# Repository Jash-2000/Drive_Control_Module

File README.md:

# Drive_Control_Module
Designed and Developed the Drive Control module for an Formula Electric car using ARM cortex processor.

---

## CAN - Controller Area Network

CAN provides four different types of message frames:

1. Data Frame – Sends data
Data transfer from one sending node to one or numerous receiving nodes.

2. Remote Frame – Requests data

Any node may request data from one source node. A remote frame is consequently followed by a data frame containing the requested data.

3. Error Frame – Reports error condition
Any bus participant, sender or receiver, may signal an error condition at any time during a data or remote frame transmission.

4. Overload Frame – Reports node overload

A node can request a delay between two data or remote frames, meaning that the overload frame can only occur between data or remote frame transmissions.

---

## Topics 

Vehicle Dynamics
```
  Wheel alignment
  Roll, yaw, pitch
  ABS
  Types of suspension, braking, brake fluid
  UV joints, rack & pinion
  Oversteer, understeer, counter-steer
  Load transfer
  Bearings
```

Aerodynamics
```
Lift & Drag (types and causes)
Centre of pressure
Coanda effect
Ground effect
Basic Airfoil terminology
Chassis and Ergonomics
Chassis Flex
Chassis stiffness
Different types of chassis
Composites used for making chassis
```

Powertrain
```
Thermodynamic cycles in engine.
All parts of engine, intake, exhaust.
Restrictor
Compression Ratio
Knocking
Torque steer elimination
CV and other types of joints
Differential: working and need
Volumetric efficiency
Chain tensioning methods
Engine tuning parameters
```

Electronics and Safety Circuits
```
Sensors
DAQ (Data Acquisition System)
T-MAP sensors
Relays
Solenoids
Shutdown/kill switches
Rectifier
Diodes
Motor and Controller
Types and working of electric motors
Torque Vectoring
Functions of motor controller
```

Battery and Battery Management System
```
Regenerative Braking
Cell Balancing, Charging/discharging profiles of battery
Power, energy density of cells
Heating and methods of temperature control
```

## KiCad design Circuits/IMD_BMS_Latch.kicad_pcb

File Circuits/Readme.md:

This file contains the Low voltage circuitary developed in order to aid the functionalities of the car. The PCB designing and routing files as well as the associated gerber files
are present here.

  * BSPD - Brake System Pausiblity Device - This Safety Critical Signal uses a pressure sensor and shuts down the car in case of hard braking. It is also integrated with the DCM
for the purpose of logitics and also cutting down the signal for torque as well.
  * IMD - Insulation Monitoring device - This device esures that 2 different lines of voltage have no leakage current.
  * TSAL - The Tractive System Active Light is a red/green indicator light that indicates the presence of high-voltage in the Tractive System. The following design for a TSAL driver is split across two modules. The High-Voltage Measurement module (HVM) and the Indicator Module (DRV). The HVM connects to the output of the AIRs, and is located in the accumulator housing. The HVM is responsible for detecting whether Tractive System voltage is above or below the safe threshold.
  * Prechargs Circuit - A device to precharge the Tractive System. This prototype features voltage feedback to protect AIRs. In open-loop systems, if a wiring fault develops (eg. precharge resistor is disconnected or discharge is stuck on) then the precharge is ineffective and AIRs may become damaged.

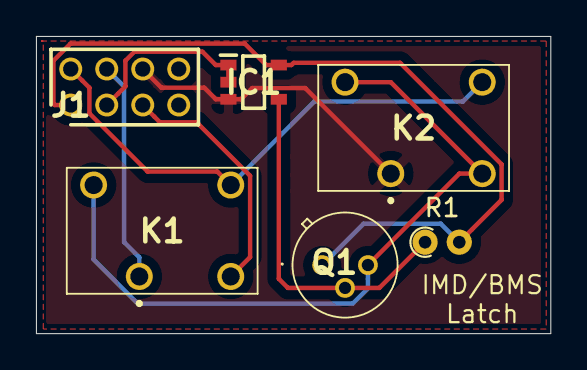
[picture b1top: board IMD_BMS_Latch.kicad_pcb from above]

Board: 2 copper layers, 28.6 x 16.5 mm, 6 parts (0 on the bottom side), 8 nets.

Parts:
IC1: BU4S11G2-TR; SOT95P280X125-5N
J1: 79107-7003; SHDR8W46P200_2X4_819X419X444P
K1, K2: G6L-1P-DC24; G6L1PDC24
Q1: BCY79; CENTRAL_TO18
R1: 10k; R_Axial_DIN0204_L3.6mm_D1.6mm_P1.90mm_Vertical

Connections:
/GND: IC1.3, J1.6, K2.2
/IMD_12V: IC1.5, J1.1, Q1.1, R1.2
/IMD_reset_button: J1.2, K1.5, K2.5
/IMD_signal: IC1.1, IC1.2, J1.3
/IN_A: J1.4, K1.2
/OUT_B: J1.5, K1.4
unnamed: K1.8, K2.4, K2.8, Q1.3
unnamed: IC1.4, Q1.2, R1.1

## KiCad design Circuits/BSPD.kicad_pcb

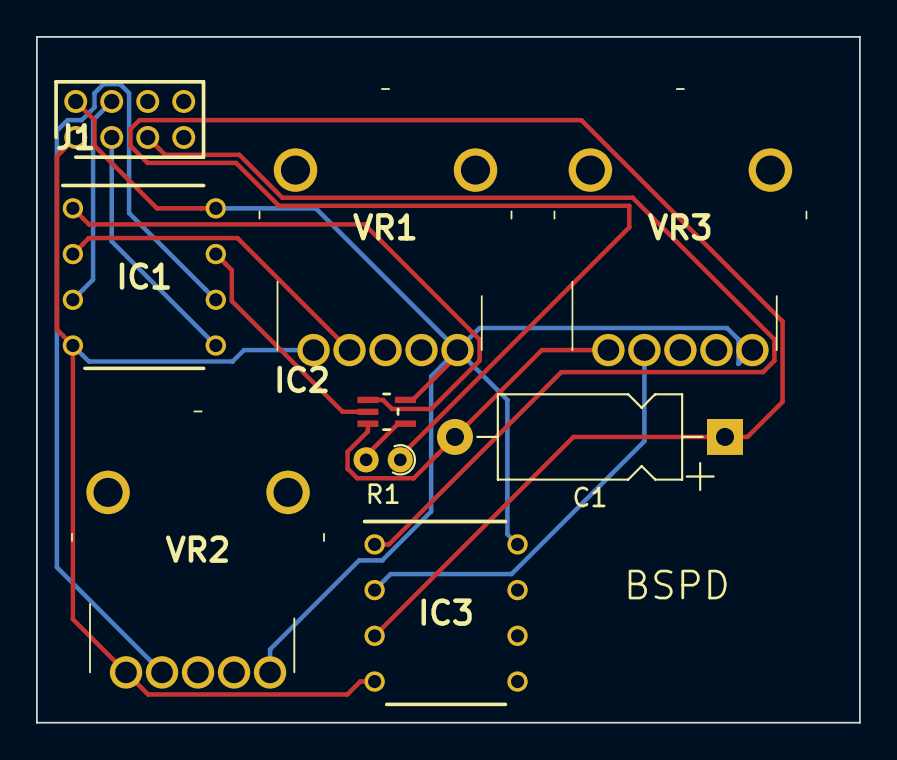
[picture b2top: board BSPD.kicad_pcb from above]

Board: 2 copper layers, 45.7 x 38.1 mm, 9 parts (0 on the bottom side), 12 nets.

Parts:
C1: 100uF; CP_Axial_L10.0mm_D4.5mm_P15.00mm_Horizontal
IC1, IC3: LM393N_NOPB; DIP794W53P254L959H508Q8N
IC2: BU4S81G2-TR; SOT65P210X110-5N
J1: 79107-7003; SHDR8W46P200_2X4_819X419X444P
R1: 500k; R_Axial_DIN0204_L3.6mm_D1.6mm_P1.90mm_Vertical
VR1, VR2, VR3: RK10J12E0A0A

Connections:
+12V: IC1.8, IC2.5, IC3.8, J1.2, VR1.3, VR2.3, VR3.3
/Curr_sensor: IC1.5, J1.3
/brake_sensor: IC1.3, J1.4
/output: IC3.1, J1.5
GND: C1.2, IC1.4, IC2.3, IC3.4, J1.1, VR1.1, VR2.1, VR3.1
unnamed: C1.1, IC3.3, R1.1
unnamed: IC1.1, IC2.1
unnamed: IC1.2, VR1.2
unnamed: IC1.6, VR2.2
unnamed: IC1.7, IC2.2
unnamed: IC2.4, R1.2
unnamed: IC3.2, VR3.2

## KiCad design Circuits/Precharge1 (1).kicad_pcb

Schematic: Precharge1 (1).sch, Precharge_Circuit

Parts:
C1: 0.1u; CP_Axial_L10.0mm_D4.5mm_P15.00mm_Horizontal
C2: 100u; CP_Axial_L10.0mm_D4.5mm_P15.00mm_Horizontal
IC1: LM555CN_NOPB; NE555DR; Mouser Part Number 926-LM555CN/NOPB
IC2: BU4S11G2-TR; SOT95P280X125-5N; Mouser Part Number 755-BU4S11G2-TR
IC3: BU4S81G2-TR; SOT65P210X110-5N; Mouser Part Number 755-BU4S81G2-TR
J1: 79107-7003; SHDR8W46P200_2X4_819X419X444P; Mouser Part Number 538-79107-7003
R1: 10k; R_Axial_DIN0204_L3.6mm_D1.6mm_P1.90mm_Vertical

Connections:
/Gnd: C1.2, C2.2, IC1.1, IC2.3, IC3.3, J1.3
/Vcc: IC1.4, IC1.8, IC2.5, IC3.5, J1.1, R1.1
/Voltage_Sensor: IC3.2, J1.4
unnamed: C1.1, IC1.5
unnamed: C2.1, IC1.6, IC1.7, R1.2
unnamed: IC1.2, J1.2
unnamed: IC1.3, IC2.1, IC2.2
unnamed: IC2.4, IC3.1
unnamed: IC3.4, J1.5

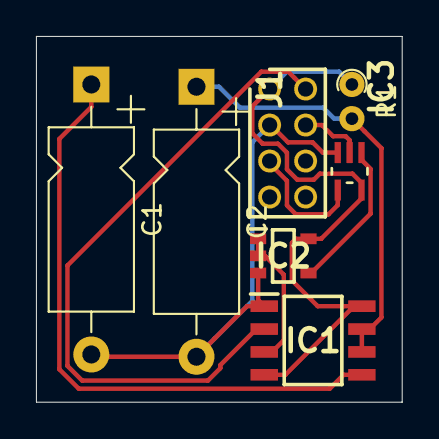
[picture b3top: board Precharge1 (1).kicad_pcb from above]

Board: 2 copper layers, 20.3 x 20.3 mm, 7 parts (0 on the bottom side), 9 nets.

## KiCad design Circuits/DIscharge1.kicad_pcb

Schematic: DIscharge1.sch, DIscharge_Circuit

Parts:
C1: 0.1u; CP_Axial_L10.0mm_D4.5mm_P15.00mm_Horizontal
C2: 100u; CP_Axial_L10.0mm_D4.5mm_P15.00mm_Horizontal
IC1: LM555CN_NOPB; NE555DR; Mouser Part Number 926-LM555CN/NOPB
J1: 79107-7003; SHDR8W46P200_2X4_819X419X444P; Mouser Part Number 538-79107-7003
R1: 10k; R_Axial_DIN0204_L3.6mm_D1.6mm_P1.90mm_Vertical
U1: SN74LS74AD; SOIC127P600X175-14N

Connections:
unnamed: C1.1, IC1.5
unnamed: C1.2, C2.2, IC1.1, J1.3, U1.1, U1.7
unnamed: C2.1, IC1.6, IC1.7, R1.2
unnamed: IC1.2, J1.2
unnamed: IC1.3, U1.3
unnamed: IC1.4, IC1.8, J1.1, R1.1, U1.2, U1.14
unnamed: J1.4, U1.5
unnamed: J1.5, U1.6

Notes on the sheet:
GNDREF
Vcc

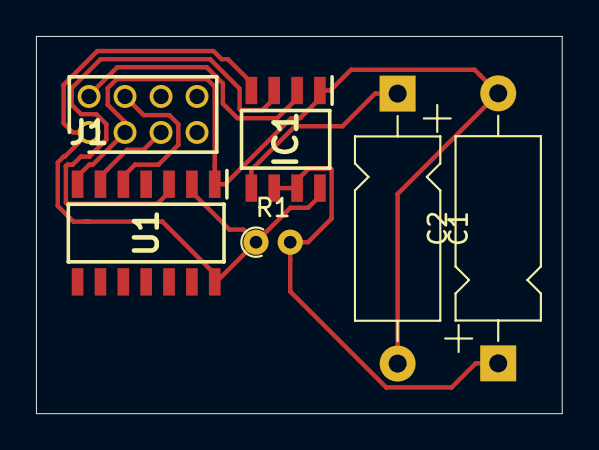
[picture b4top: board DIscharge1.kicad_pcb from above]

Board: 2 copper layers, 29.2 x 21.0 mm, 6 parts (0 on the bottom side), 8 nets.

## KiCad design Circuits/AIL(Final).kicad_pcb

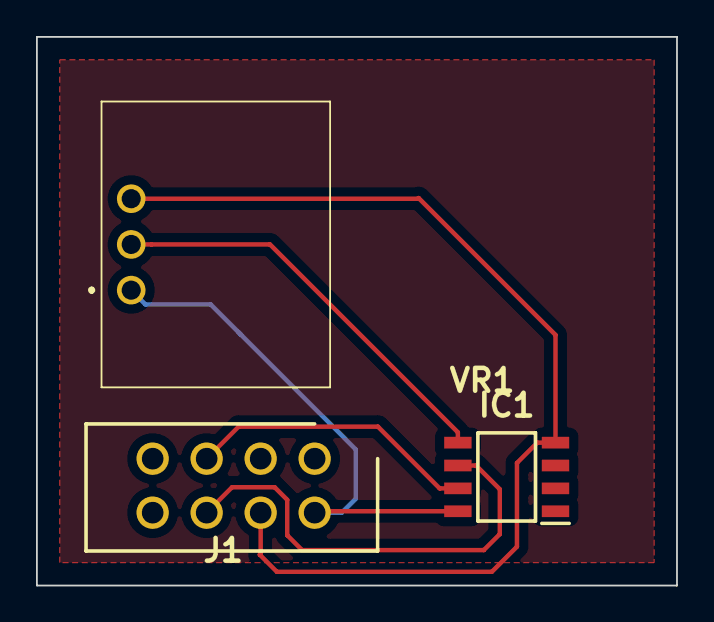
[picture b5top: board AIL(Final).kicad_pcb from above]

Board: 2 copper layers, 35.6 x 30.5 mm, 3 parts (0 on the bottom side), 5 nets.

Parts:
IC1: LM393M_NOPB; LM393
J1: 6PinConnector(TE); 8PinConnector
VR1: Potentiometer(FS); Potentiometer

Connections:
unnamed: IC1.4, J1.4, VR1.3
unnamed: IC1.5, VR1.2
unnamed: IC1.6, J1.6
unnamed: IC1.7, J1.5
unnamed: IC1.8, J1.2, VR1.1

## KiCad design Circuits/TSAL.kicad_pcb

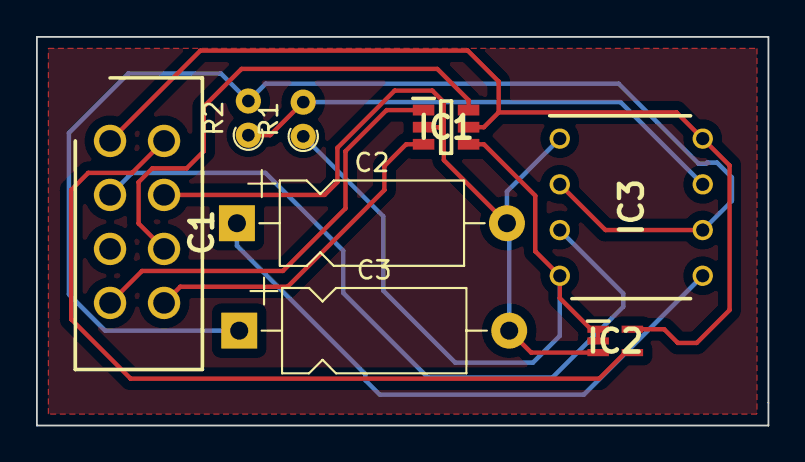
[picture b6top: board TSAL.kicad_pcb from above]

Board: 2 copper layers, 40.6 x 21.6 mm, 8 parts (0 on the bottom side), 11 nets.

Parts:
C1: 8PinConnector(TE); 8PinConnector
C2, C3: 1uFCapacitor; CP_Axial_L10.0mm_D4.5mm_P15.00mm_Horizontal
IC1: 3InputORgate; SOT95P280X145-6N
IC2: 2InputNANDGATE; SOT65P210X110-5N
IC3: LM555CMM_NOPB; LM555CN
R1: 1KOhmResistor; R_Axial_DIN0204_L3.6mm_D1.6mm_P1.90mm_Vertical
R2: 100KOhmsResistor; R_Axial_DIN0204_L3.6mm_D1.6mm_P1.90mm_Vertical

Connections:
unnamed: C1.1, IC1.5, IC2.5, IC3.8
unnamed: C1.2, IC2.4
unnamed: C1.3, IC3.3
unnamed: C1.4, C2.2, C3.2, IC1.2, IC2.3, IC3.1
unnamed: C1.6, IC1.6
unnamed: C1.7, IC1.1
unnamed: C1.8, IC1.3
unnamed: C2.1, IC3.5
unnamed: C3.1, IC3.2, IC3.6, R2.2
unnamed: IC1.4, IC2.1, IC2.2, IC3.4, R1.1
unnamed: IC3.7, R1.2, R2.1

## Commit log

2021-03-02 Added Procurement Report
2021-06-11 Added the circuit files
2021-06-11 Additional PCBs added
2021-06-11 Added Concept challenge report
2021-06-11 Create Manual
2021-06-12 Safety Circuit
2021-06-12 Control file reference
2021-07-30 Design files added
